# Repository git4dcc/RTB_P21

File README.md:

# RTB_P21

This simple module is a quad [NEM 651](https://www.morop.org/downloads/nem/de/nem651_d.pdf) socket decoder test board and is part of my growing collection of tools for my DCC based digital model trains. The board has four independent NEM651 sockets and the DCC signal is fed in and out at both ends for daisy-chaining multiple boards. For each, a motor or resistor can be connected externally to enable service mode programming with DCC.

<details>
<summary>See also</summary>

- [RTB_D16](/../../../../git4dcc/RTB_D16) (DCC Decoder)
- [RTB_D20](/../../../../git4dcc/RTB_D20) (DCC Decoder)
- [RTB_P24](/../../../../git4dcc/RTB_P24)
- [RTB_P27](/../../../../git4dcc/RTB_P27)

</details>

<details>
<summary>User Guides</summary>

- User Guide - DE (to be done)
- User Guide - EN (to be done)

</details>

# Hardware
My PCB layout uses SMD footprints with mainly 0603 parts. With some experience handsoldering is good to use.

## PCB
- 2-layer PCB, FR4, 1.6mm
- Dimensions: 80mm x 22mm
- 4x [NEM 651](https://www.morop.org/downloads/nem/de/nem651_d.pdf) decoder sockets

## Kicad
[Schematic](doc/P21_schematic.pdf) | [Layout](doc/P21_layout.pdf) | [Gerber](gerber/P21_0.zip)

<details>
<summary>Dependency</summary>
<br>

:yellow_circle: Requires my Kicad project library [RTB_SamacSys](/../../../../git4dcc/RTB_SamacSys) in the same directory tree.

</details>

# Images

This project is intended for hobby use only and is distributed in accordance with the Apache License 2.0 agreement.

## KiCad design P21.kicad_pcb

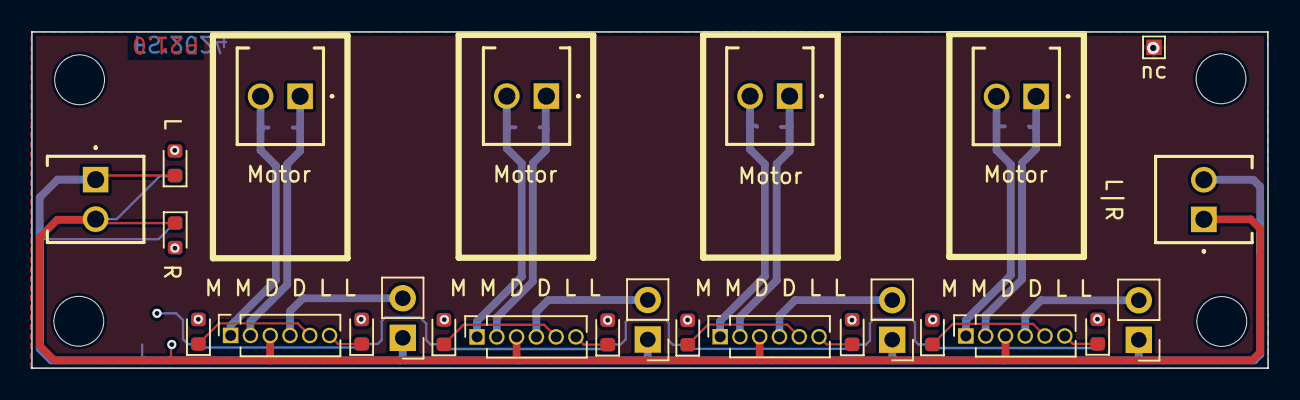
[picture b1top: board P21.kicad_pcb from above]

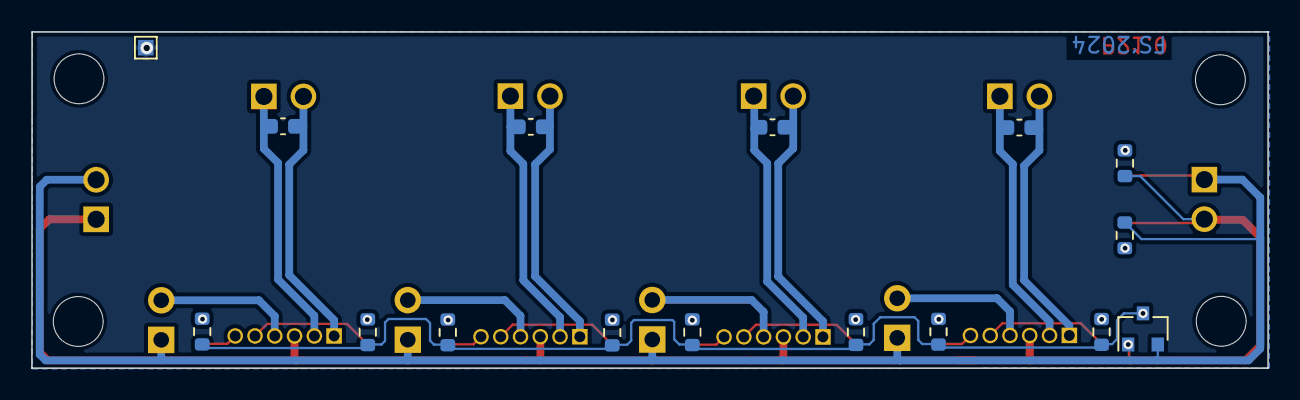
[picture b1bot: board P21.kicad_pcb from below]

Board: 2 copper layers, 79.4 x 21.6 mm, 45 parts (16 on the bottom side), 34 nets.

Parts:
C1, C2, C3, C4: 47p; C_0603_1608Metric
D1: BAT54C; SOT-23
D2, D3, D4, D5, D6, D7, D8, D9, D10, D11: LED_Small_ALT; LED_0603_1608Metric
H1, H2, H3, H4: MountingHole; MountingHole_3.2mm_M3_DIN965
J1, J2, J3, J4: NEM 651; PinSocket_1x06_P1.27mm_Vertical
J5, J6, J7, J8: Conn_01x02; PinHeader_1x02_P2.54mm_Vertical
J9, J10: DCC; 1725656
J11, J12, J13, J14: Conn_01x03_Male; 1725656
J15, J16: Conn_01x01; TestPoint_Pad_1.0x1.0mm
R1, R2, R3, R4, R5, R6, R7, R8, R9, R10: 10k; R_0603_1608Metric

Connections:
NC: J15.1, J16.1
unnamed: C1.1, J3.2, J11.1
unnamed: C1.2, J3.1, J11.2
unnamed: C2.1, J4.2, J12.1
unnamed: C2.2, J4.1, J12.2
unnamed: C3.1, J1.2, J13.1
unnamed: C3.2, J1.1, J13.2
unnamed: C4.1, J2.2, J14.1
unnamed: C4.2, J2.1, J14.2
unnamed: D1.1, D10.1, J1.3, J2.3, J3.3, J4.3, J9.1, J10.2, R10.2
unnamed: D1.2, D11.1, J5.1, J6.1, J7.1, J8.1, J9.2, J10.1, R9.2
unnamed: D1.3, R1.2, R2.2, R3.2, R4.2, R5.2, R6.2, R7.2, R8.2
unnamed: D2.1, J3.6
unnamed: D2.2, R1.1
unnamed: D3.1, J3.5
unnamed: D3.2, R2.1
unnamed: D4.1, J2.6
unnamed: D4.2, R3.1
unnamed: D5.1, J2.5
unnamed: D5.2, R4.1
unnamed: D6.1, J1.6
unnamed: D6.2, R5.1
unnamed: D7.1, J1.5
unnamed: D7.2, R6.1
unnamed: D8.1, J4.6
unnamed: D8.2, R7.1
unnamed: D9.1, J4.5
unnamed: D9.2, R8.1
unnamed: D10.2, R9.1
unnamed: D11.2, R10.1
unnamed: J1.4, J6.2
unnamed: J2.4, J7.2
unnamed: J3.4, J8.2
unnamed: J4.4, J5.2

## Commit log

2024-10-11 initial
2026-02-20 Update links in README.md to relative paths
2026-02-20 git mirror test
